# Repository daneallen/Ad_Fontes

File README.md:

# Ad Fontes STEM Project 2025

A project intended to introduce students to electrical engineering, printed circuit
board (PCB) design, soldering and embedded microcontroller programming.

# Day 1

Introduction to circuit design of the project. The entire design of the PCB was
completed using [KiCad](https://www.kicad.org/), a free and open sourced PCB software application.

The design of the circuit is built around the small and very capable [ATtiny1616](https://ww1.microchip.com/downloads/en/DeviceDoc/ATtiny1614-16-17-DataSheet-DS40002204A.pdf) microcontroller.

The entire schematic of the PCB is [here](/Documents/Schematic.pdf)

## Design Timeline

| Date | Notes |
| ------ | ----------- |
| 8/23/25 | The PCB was first designed in KiCad |
| 8/28/25 | The first order of PCBs was placed. |
| 9/15/25 | The first of PCBs arrives. The design was sound, however the logo was too dark and there was improvements that could be made |
| 9/19/25 | Order #2 (v02) was placed to fix some of the identified issues |
| 10/6/25 | v02 badges arrive, Overall good, would benefit from a few additional things printed on the back of the board. |
| 10/19/25 | Order #3 (v03) was placed |
| 10/30/25 | v03 badge arrives. There is a problem with the back grounding plane... it was NOT filled in and so nothing works. |
| 11/10/25 | Order #4 (v04) was placed to finally fix all the things. |
| 11/20/25 | v04 arrives and is functional and ready for class. |

### Ideas for improvement

   - [x] lighten the colors for on the front of the badge for more contrast
   - [x] enlarge the test on the back of the badge... possibly expand/point out the different components
   - [x] remove the svg2mod on the front silkscreen
   - [x] better align the image on the front of the badge
   - [x] fix/address/remove the white parts near the mouse bites
   - [x] add a box and label for initials

# Day 2

On this day students will select the 4 LEDs that will be soldered onto their PCB.

Basic Steps for Soldering:
   1. Introduce Heat
   2. Introduce Solder
   3. Remove the Solder
   4. Remove the Heat  

[YouTube Link for Soldering Example](https://www.youtube.com/watch?v=eHu_fGAyNY4)

# Day 3

Time to finish the PCB with some custom firmware. The ATtiny1616 utilizes the [Unified Program and Debug Interface (UPDI)]([https://learn.adafruit.com/adafruit-updi-friend/overview) protocol to program the microcontroller. Having the [Adafruit UPDI Friend Programmer](https://www.adafruit.com/product/5879) is quite helpful, especially when using it with the Tag-Connect [TC2030-IDC-NL](https://www.tag-connect.com/product/tc2030-idc-nl) 6-pin plug-of-nails connector tool.

## Programming the Badge

Programming the board is accomplished by using the interactive [programming script](/Arduino/Programming/programming.sh).

Available options are for the board to boot up into one of the following options:
1. Steady On all LEDs
2. Twinkle Effect
3. Chase Effect
4. Breathing Effect

## Source Code

[Source Code](/Arduino/adFontes) for the board.

## Behind the Scenes

You will notice that there numerous components already assembled on the board prior to the 4 LEDs. Those components were assembled
in the following manner.

1. Setup the PCB in a jig to apply the solder paste.

2. Apply the solder paste to the PCB.

3. Setup the Pick and Place Machine and have it place all the small components to the board.
[Watch the PnP magic](/Images/Assembly/PnP.mp4)

4. Add the larger components by hand.
<br>

5. Put the board in the oven.

6. Wait about 6 minutes for a freshly cooked badge to come out completed on the other side.
[Cooked badge](/Images/Assembly/ovenFinished.mov)

7. Pick your favorite 4 LED colors, solder them on and enjoy.

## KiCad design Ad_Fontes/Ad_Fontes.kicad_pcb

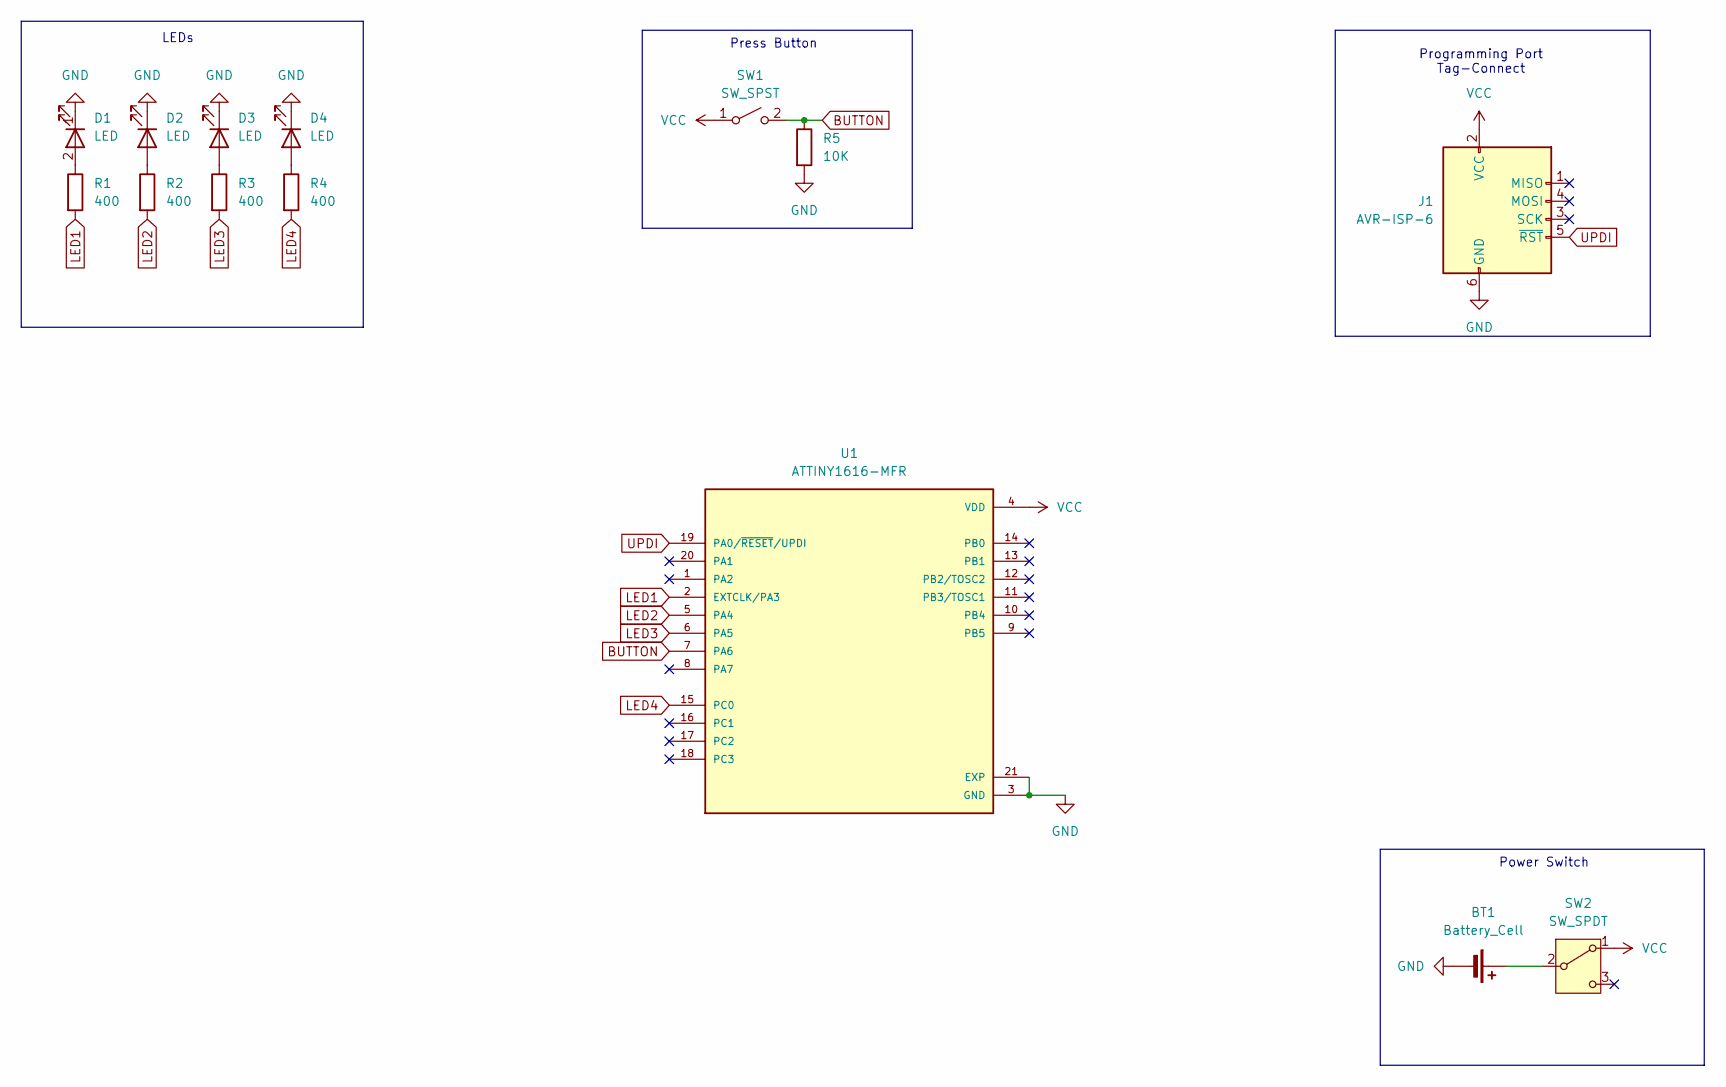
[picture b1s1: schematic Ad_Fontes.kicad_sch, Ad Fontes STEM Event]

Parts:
BT1: Battery_Cell; BatteryHolder_Keystone_3034_1x20mm
D1, D2, D3, D4: LED; LED_D3.0mm
J1: AVR-ISP-6; TAG_TC2030-IDC-NL
R1, R2, R3, R4: 400; R_0805_2012Metric_Pad1.20x1.40mm_HandSolder
R5: 10K; R_0805_2012Metric_Pad1.20x1.40mm_HandSolder
SW1: SW_SPST; PTS526
SW2: SW_SPDT; switch_JS202011SCQN
U1: ATTINY1616-MFR; QFN40P300X300X90-21N; PARTREV A; DigiKey_Part_Number ATTINY1616-MFRTR-ND

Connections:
BUTTON: R5.1, SW1.2 (B), U1.7 (PA6)
GND: BT1.2 (-), D1.1 (K), D2.1 (K), D3.1 (K), D4.1 (K), J1.6 (GND), R5.2, U1.3 (GND), U1.21 (EXP)
LED1: R1.2, U1.2 (EXTCLK/PA3)
LED2: R2.2, U1.5 (PA4)
LED3: R3.2, U1.6 (PA5)
LED4: R4.2, U1.15 (PC0)
unnamed: BT1.1 (+), SW2.2 (B)
unnamed: D1.2 (A), R1.1
unnamed: D2.2 (A), R2.1
unnamed: D3.2 (A), R3.1
unnamed: D4.2 (A), R4.1
UPDI: J1.5 (~RST), U1.19 (PA0/~RESET/UPDI)
VCC: J1.2 (VCC), SW1.1 (A), SW2.1 (A), U1.4 (VDD)

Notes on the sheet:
Press Button
LEDs
Programming Port Tag-Connect
Power Switch

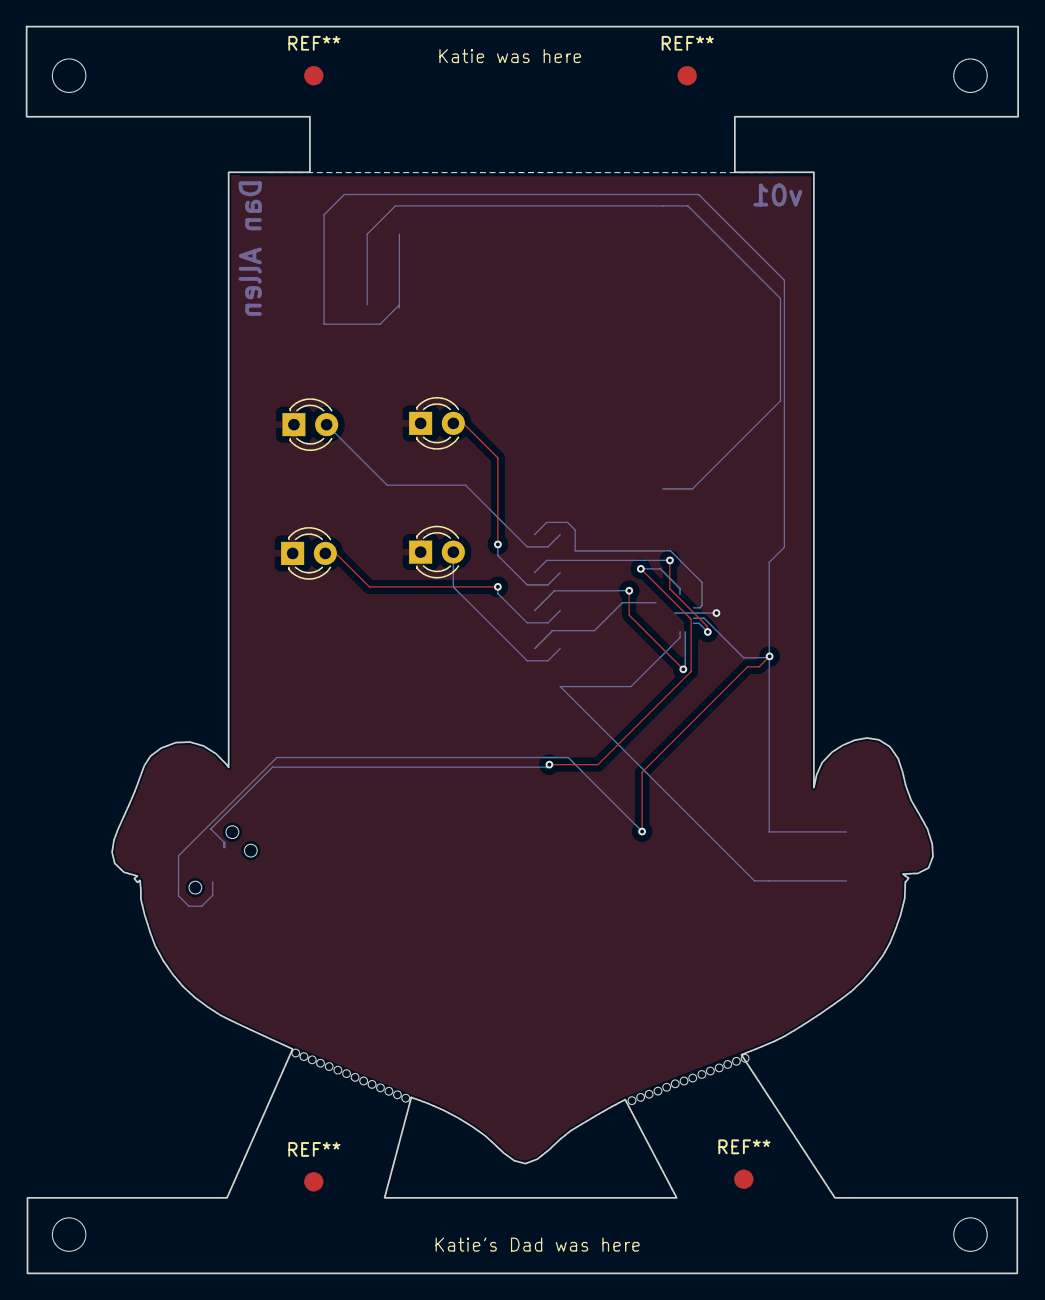
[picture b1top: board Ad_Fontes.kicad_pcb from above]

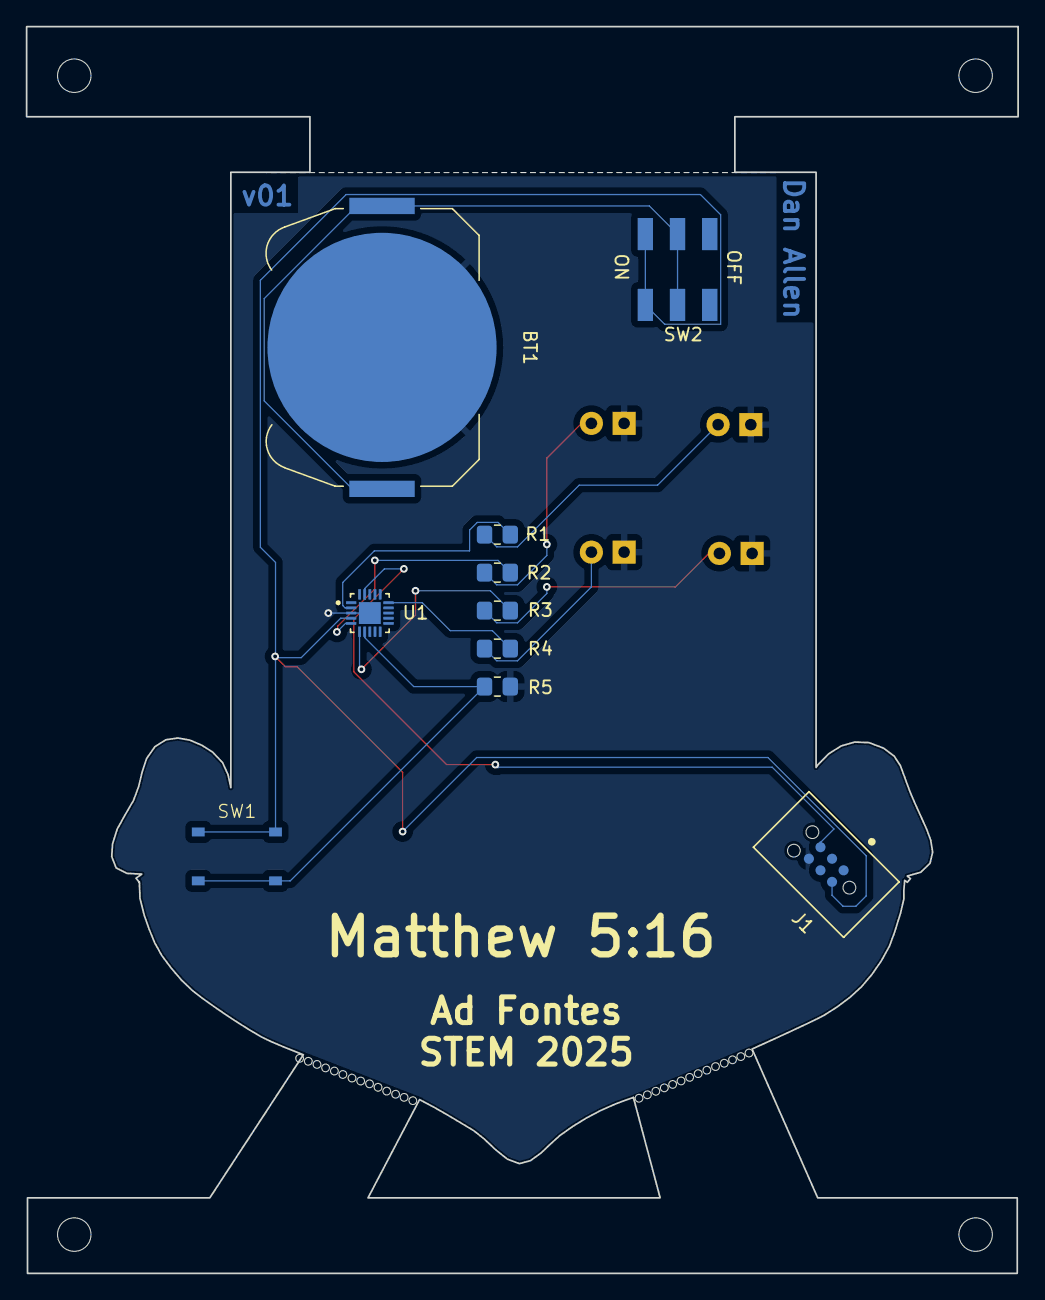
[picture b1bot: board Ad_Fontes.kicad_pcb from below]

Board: 2 copper layers, 77.0 x 96.8 mm, 15 parts (10 on the bottom side), 13 nets.

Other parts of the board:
svg2mod: G***; Ad Fontes Crest Logo

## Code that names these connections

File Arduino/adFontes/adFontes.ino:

/* Ad Fontes STEM Badge 2025
 * 
 * author: @cybertestpilot
 * 
 */

#include <SoftwareTimer.h>

// The definitions of the pins mapped to the MCU
#define LED1 PIN_PA3
#define LED2 PIN_PA4
#define LED3 PIN_PA5
#define LED4 PIN_PC0
#define BUTTON A6


int led_array[4] = {LED1, LED2, LED3, LED4};
int led_array_index = 0;

int buttonState;            // the current reading from the input pin
int lastButtonState = LOW;  // the previous reading from the input pin

unsigned long lastDebounceTime = 0;  // the last time the output pin was toggled
unsigned long debounceDelay = 50;

// The initial value the board is set to for the purposes of the the LED initial state
int LED_STATE = 9;

int delay_value = 0;

// The delay value being used to set the twinkle effect of the random blinking
bool doTwinkle = false;
bool doDelay = false; 
unsigned long delayStart = 0;
unsigned long delayLenFast = 100;

void twinkleEffect();
SoftwareTimer twinkleTimer(100, &twinkleEffect);

void chaseEffect();
SoftwareTimer chaseTimer(200, &chaseEffect);
bool doChase = false;
int chaseIndex = 0;
int led_chase_array[4] = {LED1, LED2, LED4, LED3};

void breatheEffect();
SoftwareTimer breathTimer(15, &breatheEffect);
bool doBreathe = false;
int breathValue = 1;
int breathDir = 1;


void setup() {
  
  // put your setup code here, to run once:
  pinMode(LED1, OUTPUT);
  pinMode(LED2, OUTPUT);
  pinMode(LED3, OUTPUT);
  pinMode(LED4, OUTPUT);
  
  pinMode(BUTTON, INPUT);  
}

void twinkleEffect(){
  if(doTwinkle == true){
    for(int i=0; i<4; i++){
      analogWrite(led_array[i], random(1,255));
    }
  }
}

void chaseEffect(){
  if(doChase == true){
    for(int i=0; i<4; i++){
      if(i == chaseIndex){
        digitalWrite(led_chase_array[i], HIGH);
      }else{
        digitalWrite(led_chase_array[i], LOW);
      }
    }
    chaseIndex += 1;
    if(chaseIndex >= 4){
      chaseIndex = 0;
    }
  }
}

void breatheEffect(){
  if(doBreathe == true){
    for(int i=0; i<4; i++){
      analogWrite(led_array[i], breathValue);
    }
    breathValue += 1*breathDir;

    if(breathValue >= 250){
      breathDir = -1;
    }
    if(breathValue <= 10){
      breathDir = 1;
    }
  }
}


void loop() {
  // put your main code here, to run repeatedly:
  
  int reading = digitalRead(BUTTON);  // Read the value/state of the Button pin to see if it's been pressed

  // If the switch changed, due to noise or pressing:
  if (reading != lastButtonState) {
    lastDebounceTime = millis();  // reset the debouncing timer
  }

  if ((millis() - lastDebounceTime) > debounceDelay) {
    // whatever the reading is at, it's been there for longer than the debounce
    // delay, so take it as the actual current state:

    // if the button state has changed:
    if (reading != buttonState) {
      buttonState = reading;      

      // only toggle the LED if the new button state is HIGH
      if (buttonState == HIGH) {
        

        LED_STATE += 1;

        if(LED_STATE >= 10){
          LED_STATE = 0;
        }

        delay_value += 30;
        if(delay_value >= 255){
          delay_value = 1;
        }        
      }
    }
  }

  switch (LED_STATE) {
    case 0:
      doBreathe = false;
      digitalWrite(LED1, HIGH);
      digitalWrite(LED2, HIGH);
      digitalWrite(LED3, HIGH);
      digitalWrite(LED4, HIGH);      
      break;
    case 1:
      digitalWrite(LED1, HIGH);
      digitalWrite(LED2, LOW);
      digitalWrite(LED3, LOW);
      digitalWrite(LED4, HIGH);
      break;
    case 2:
      digitalWrite(LED1, LOW);
      digitalWrite(LED2, HIGH);
      digitalWrite(LED3, HIGH);
      digitalWrite(LED4, LOW);
      break;
    case 3:
      digitalWrite(LED1, HIGH);
      digitalWrite(LED2, LOW);
      digitalWrite(LED3, LOW);
      digitalWrite(LED4, LOW);
      break;
    case 4:
      digitalWrite(LED1, LOW);
      digitalWrite(LED2, HIGH);
      digitalWrite(LED3, LOW);
      digitalWrite(LED4, LOW);
      break;
    case 5:
      digitalWrite(LED1, LOW);
      digitalWrite(LED2, LOW);
      digitalWrite(LED3, HIGH);
      digitalWrite(LED4, LOW);
      break;
    case 6:
      digitalWrite(LED1, LOW);
      digitalWrite(LED2, LOW);
      digitalWrite(LED3, LOW);
      digitalWrite(LED4, HIGH);
      break;
    case 7: //twinkle effect
      doTwinkle = true;
      break;
    case 8: //chase effect
      doTwinkle = false;
      doChase = true;
      break;
    case 9: //breath effect
      doChase = false;
      doBreathe = true;
    default:
      break;
          
  }

  // save the reading. Next time through the loop, it'll be the lastButtonState:
  lastButtonState = reading;

  twinkleTimer.tick();
  chaseTimer.tick();
  breathTimer.tick();
}

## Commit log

2025-11-11 adding pictures
2025-11-29 Cleaning up and adding documention
2025-11-29 url changes
2025-11-29 added smaller video
2025-11-29 updated README urls
2025-11-29 additional pictures
2025-12-14 Added programming script and binaries
2025-12-15 programming picture
